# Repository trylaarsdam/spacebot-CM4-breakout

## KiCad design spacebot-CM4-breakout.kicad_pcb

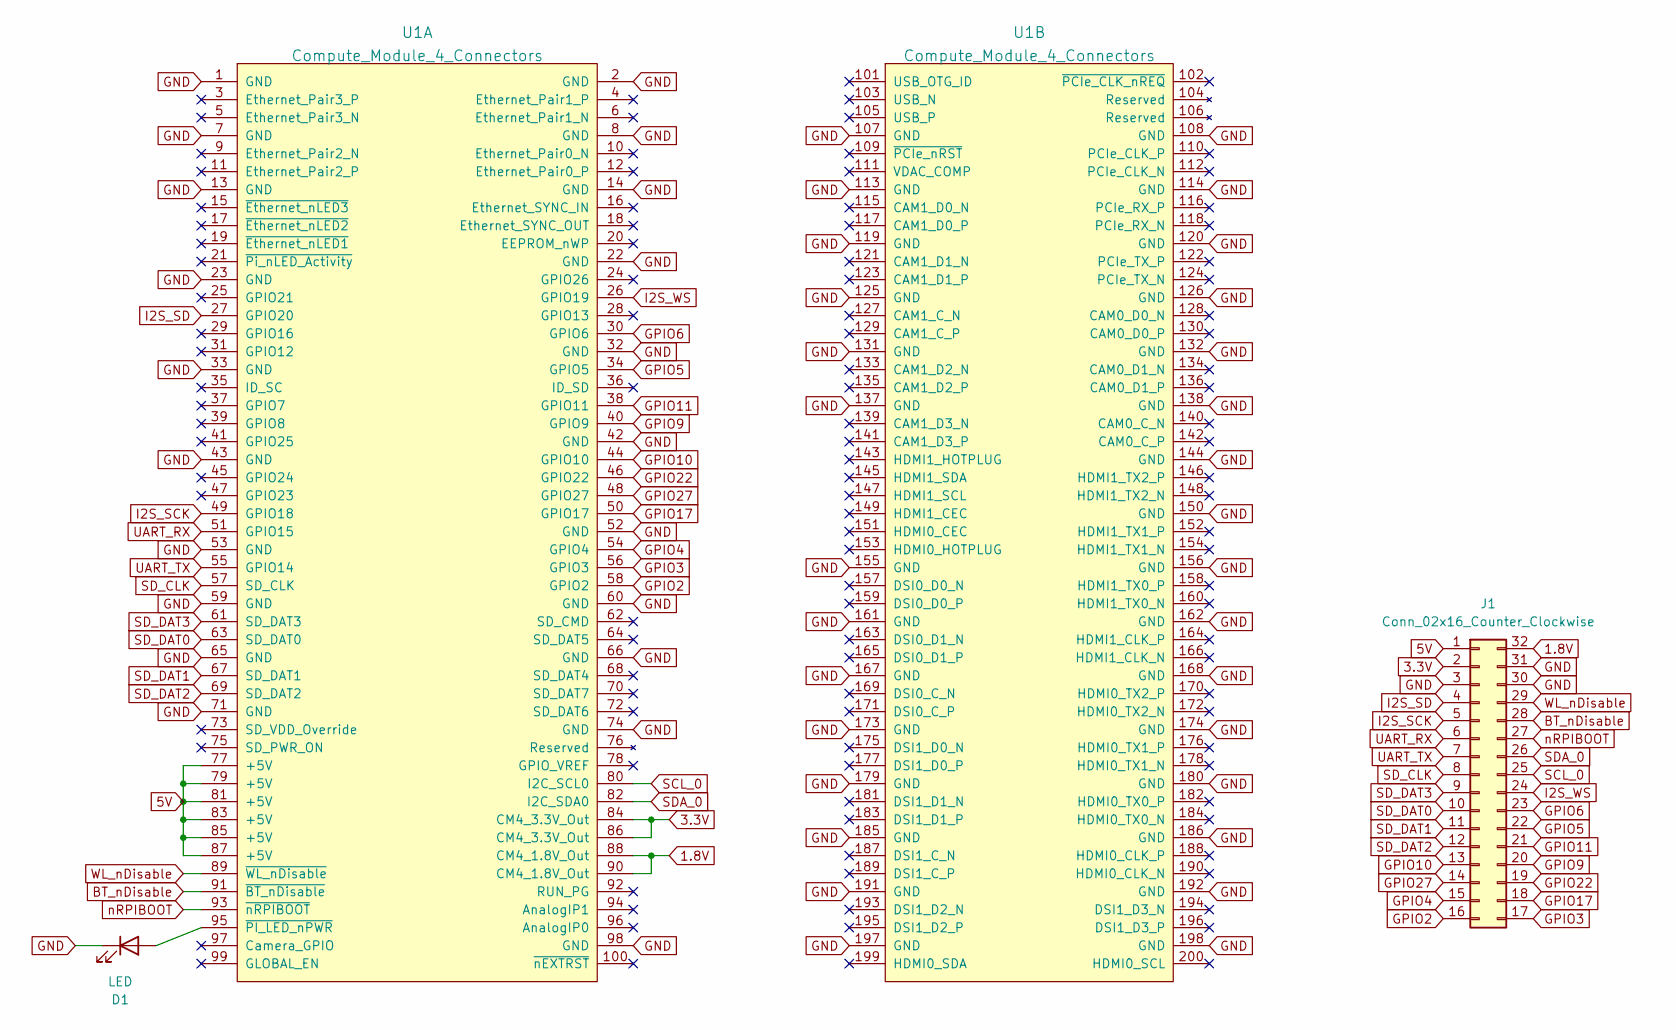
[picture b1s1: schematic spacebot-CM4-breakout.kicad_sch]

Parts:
D1: LED; LED_D3.0mm
J1: Conn_02x16_Counter_Clockwise; PinHeader_2x16_P2.54mm_Horizontal
U1: Compute_Module_4_Connectors; Raspberry-Pi-4-Compute-Module

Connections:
1.8V: J1.32, U1.88 (CM4_1.8V_Out), U1.90 (CM4_1.8V_Out)
3.3V: J1.2, U1.84 (CM4_3.3V_Out), U1.86 (CM4_3.3V_Out)
5V: J1.1, U1.77 (+5V), U1.79 (+5V), U1.81 (+5V), U1.83 (+5V), U1.85 (+5V), U1.87 (+5V)
BT_nDisable: J1.28, U1.91 (~BT_nDisable)
GND: D1.1 (K), J1.3, J1.30, J1.31, U1.1 (GND), U1.2 (GND), U1.7 (GND), U1.8 (GND), U1.13 (GND), U1.14 (GND), U1.22 (GND), U1.23 (GND), U1.32 (GND), U1.33 (GND), U1.42 (GND), U1.43 (GND), U1.52 (GND), U1.53 (GND), U1.59 (GND), U1.60 (GND), U1.65 (GND), U1.66 (GND), U1.71 (GND), U1.74 (GND), U1.98 (GND), U1.107 (GND), U1.108 (GND), U1.113 (GND), U1.114 (GND), U1.119 (GND), U1.120 (GND), U1.125 (GND), U1.126 (GND), U1.131 (GND), U1.132 (GND), U1.137 (GND), U1.138 (GND), U1.144 (GND), U1.150 (GND), U1.155 (GND), U1.156 (GND), U1.161 (GND), U1.162 (GND), U1.167 (GND), U1.168 (GND), U1.173 (GND), U1.174 (GND), U1.179 (GND), U1.180 (GND), U1.185 (GND), U1.186 (GND), U1.191 (GND), U1.192 (GND), U1.197 (GND), U1.198 (GND)
GPIO2: J1.16, U1.58 (GPIO2)
GPIO3: J1.17, U1.56 (GPIO3)
GPIO4: J1.15, U1.54 (GPIO4)
GPIO5: J1.22, U1.34 (GPIO5)
GPIO6: J1.23, U1.30 (GPIO6)
GPIO9: J1.20, U1.40 (GPIO9)
GPIO10: J1.13, U1.44 (GPIO10)
GPIO11: J1.21, U1.38 (GPIO11)
GPIO17: J1.18, U1.50 (GPIO17)
GPIO22: J1.19, U1.46 (GPIO22)
GPIO27: J1.14, U1.48 (GPIO27)
I2S_SCK: J1.5, U1.49 (GPIO18)
I2S_SD: J1.4, U1.27 (GPIO20)
I2S_WS: J1.24, U1.26 (GPIO19)
unnamed: D1.2 (A), U1.95 (~PI_LED_nPWR)
SCL_0: J1.25, U1.80 (I2C_SCL0)
SDA_0: J1.26, U1.82 (I2C_SDA0)
SD_CLK: J1.8, U1.57 (SD_CLK)
SD_DAT0: J1.10, U1.63 (SD_DAT0)
SD_DAT1: J1.11, U1.67 (SD_DAT1)
SD_DAT2: J1.12, U1.69 (SD_DAT2)
SD_DAT3: J1.9, U1.61 (SD_DAT3)
UART_RX: J1.6, U1.51 (GPIO15)
UART_TX: J1.7, U1.55 (GPIO14)
WL_nDisable: J1.29, U1.89 (~WL_nDisable)
nRPIBOOT: J1.27, U1.93 (~nRPIBOOT)

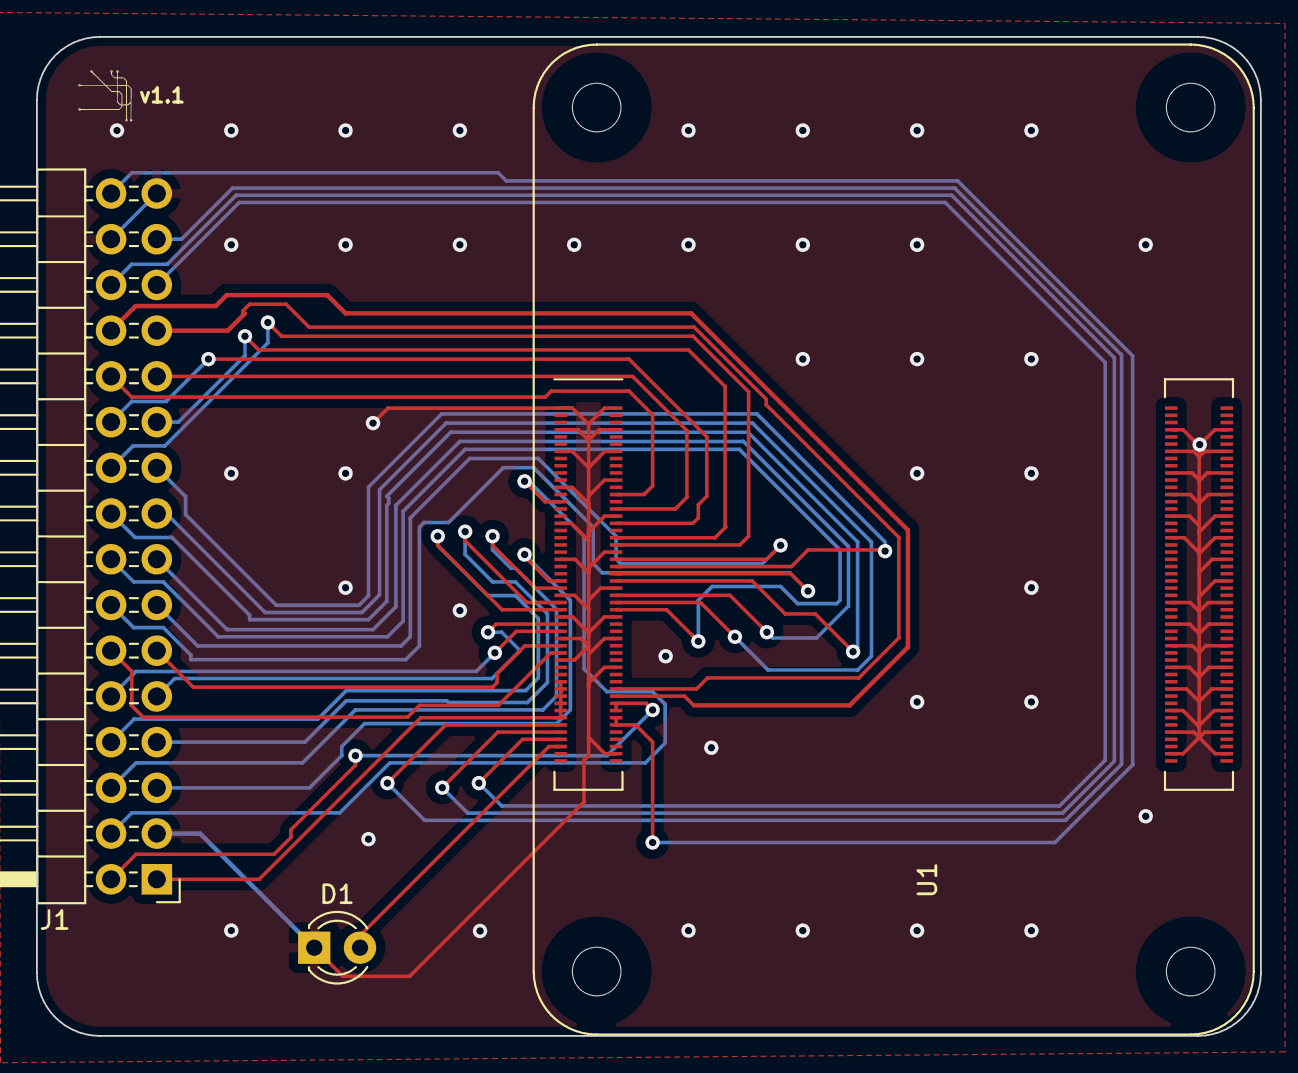
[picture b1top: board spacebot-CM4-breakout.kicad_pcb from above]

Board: 2 copper layers, 68.0 x 55.5 mm, 3 parts (0 on the bottom side), 31 nets.

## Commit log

2022-03-30 init
